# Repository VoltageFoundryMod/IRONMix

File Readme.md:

# IRONMix Eurorack Module

## Overview

Voltage Foundry Modular _IRONMix_ is a dual-function Eurorack Module in 4HP. It is a line in mixer with 2 stereo inputs and Left/Right modular-level outputs and in it's lower section it is an output module with Left/Right modular-level inputs and a stereo output capable of driving headphones or line-level gear.

## Features and Tips

- Two sections which can be used independently or together: a line in section and an output section.
- Line-in section with two stereo inputs, level controls, up to 40dB of gain, and 1MΩ input impedance and left/right modular-level outputs.
- Output section with two modular-level inputs for Left and Right channels, and a stereo output with volume control.
- Line level input is normalized to the output section, allowing the module to be used as a 2 stereo ins to stereo out mixer.
- Input section can be configured to accept line level or modular level signals, allowing the module to be used as a 2x left + 2x right mixer with modular level signals on the inputs and headphone/line level signals on the output.
- Output section right channel can be configured to be normalized to the left channel, allowing mono signals to be turned into stereo signals or normalized to the input section, allowing the module to be used as a 2 stereo ins to stereo out mixer.
- Stereo jacks on input section can be split with a stereo to 2x mono patch cable, allowing the module to be used as a 2x left + 2x right mixer with modular level signals on the inputs and headphone/line level signals on the output.

Check the module on [ModularGrid](https://modulargrid.net/e/other-unknown-ironmix-by-voltage-foundry-modular).

## Usage

For more details and usage instructions, see [Manual.md](Manual.md).

## Contact

For support and inquiries, please open an issue on the [GitHub repository](https://github.com/VoltageFoundryMod/IRONMix).

## License

This project is licensed under the MIT License. See the `LICENSE` file for more information.

---

Thank you for choosing the IRONMix module. We hope it enhances your musical creativity and performance.

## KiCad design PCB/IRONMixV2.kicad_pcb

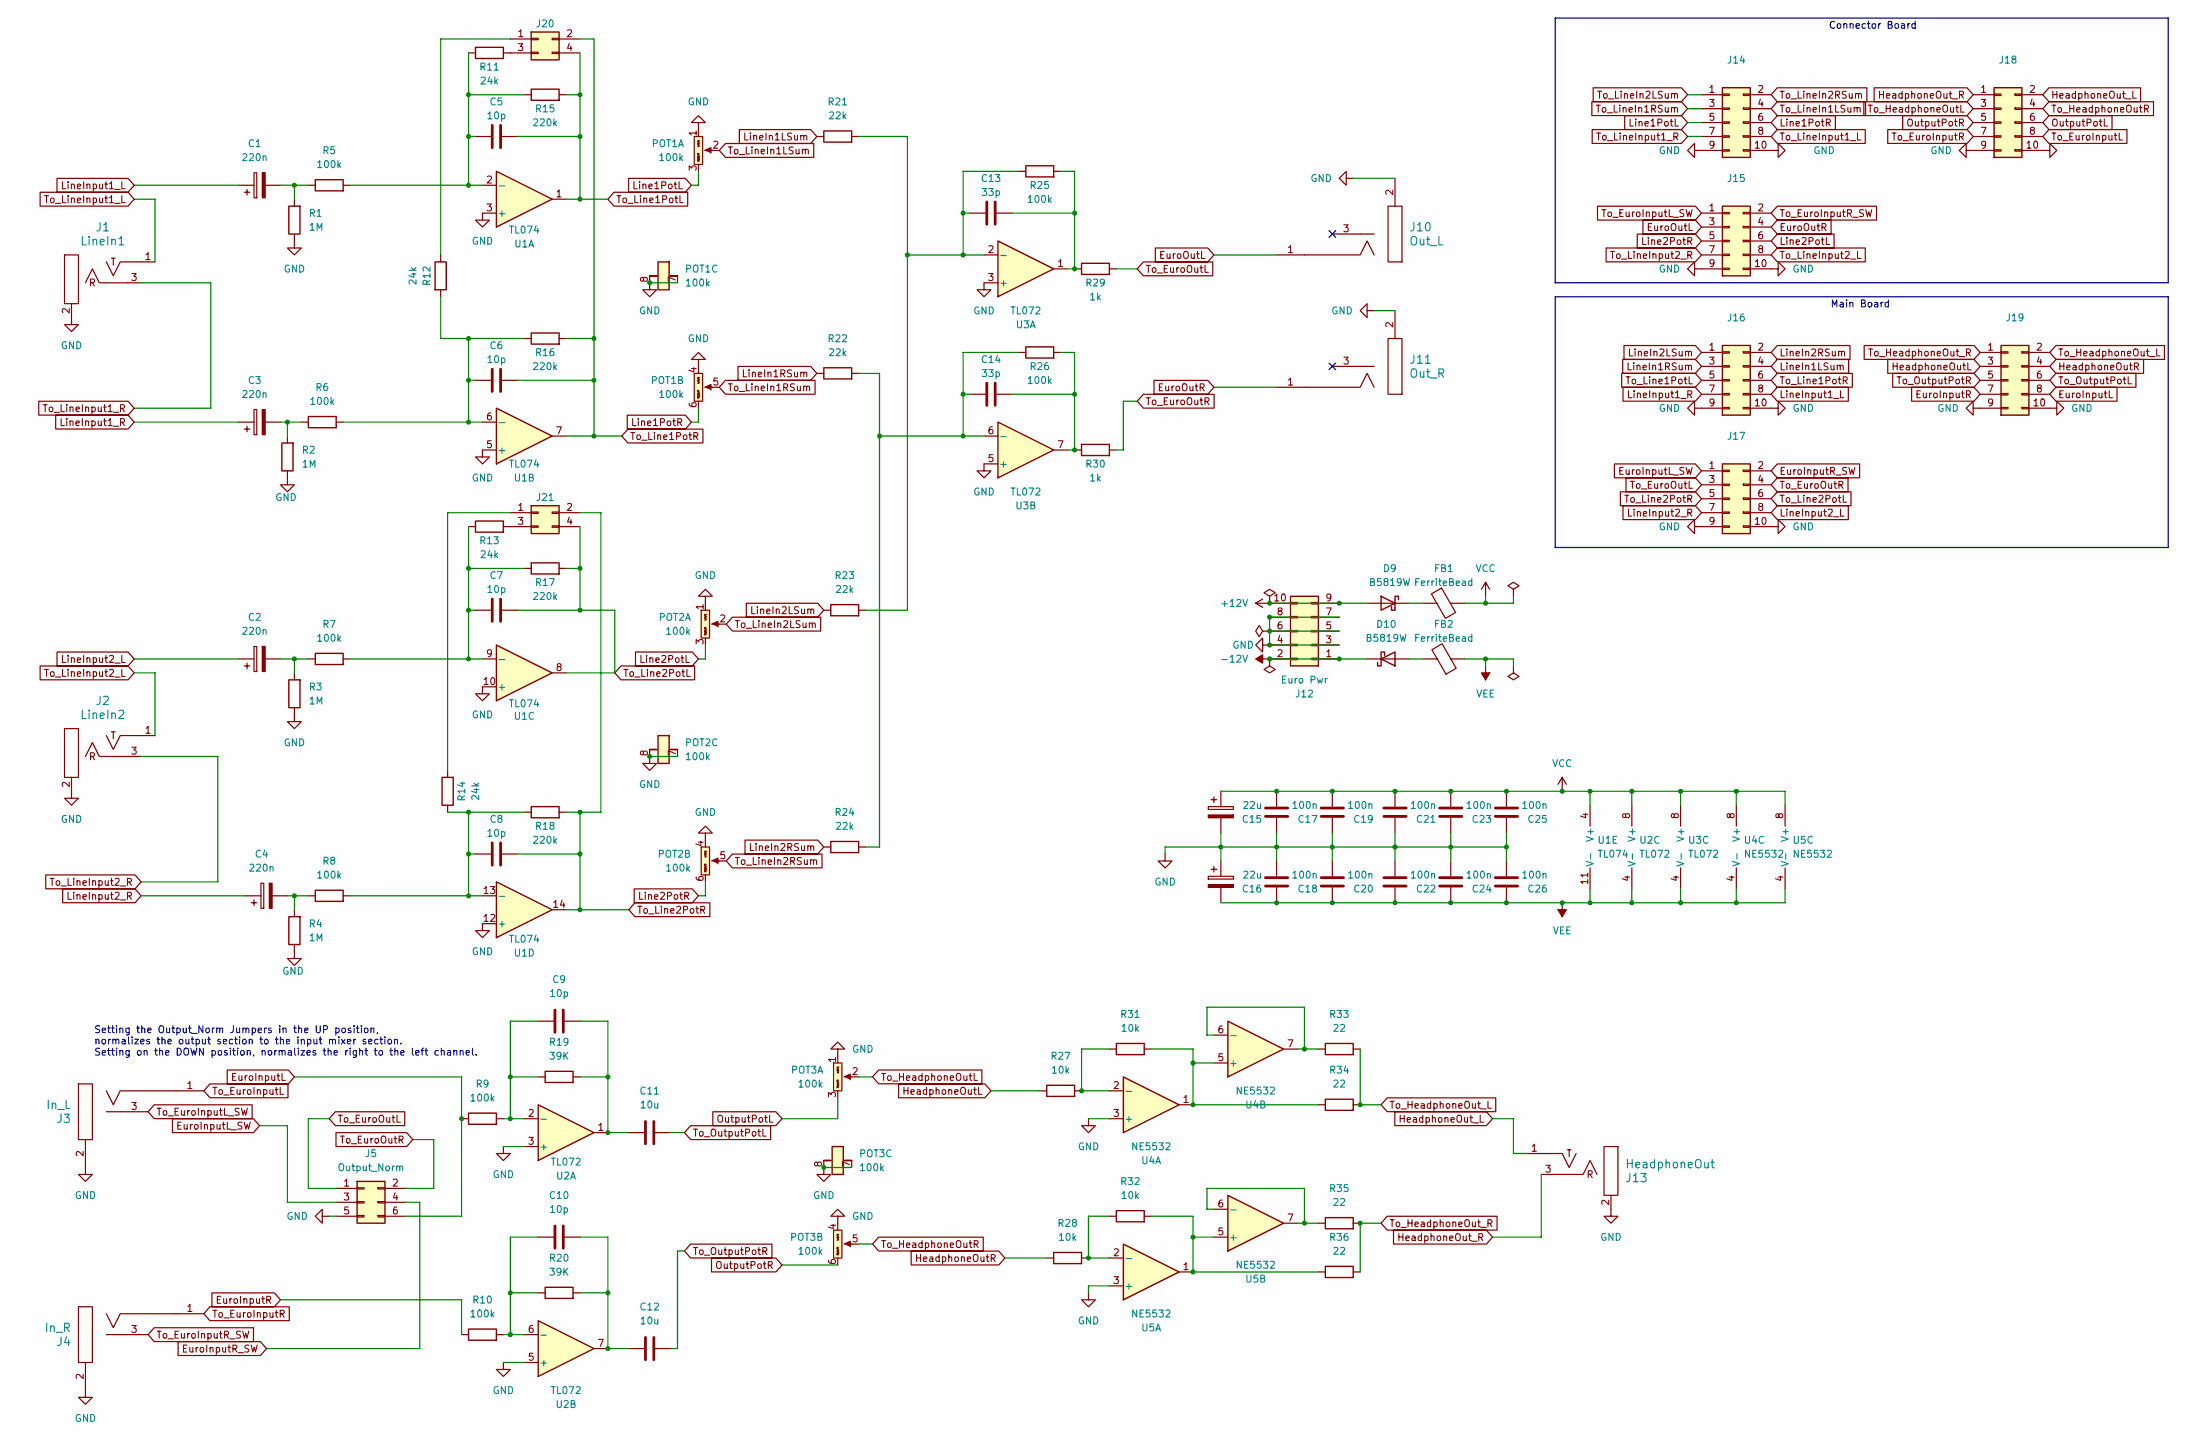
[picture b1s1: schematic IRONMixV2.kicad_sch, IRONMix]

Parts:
C1, C2, C3, C4: 220n; C_0805_2012Metric
C5, C6, C7, C8, C9, C10: 10p; C_0603_1608Metric
C11, C12: 10u; C_0603_1608Metric
C13, C14: 33p; C_0603_1608Metric
C15, C16: 22u; CP_Elec_6.3x4.5
C17, C18, C19, C20, C21, C22, C23, C24, C25, C26: 100n; C_0603_1608Metric
D9, D10: B5819W; D_SOD-123
FB1, FB2: FerriteBead; L_0805_2012Metric
J1: LineIn1; EighthInch_Stereo_PJ366ST; Part Number WQP-WQP419GR
J2: LineIn2; EighthInch_Stereo_PJ366ST; Part Number WQP-WQP419GR
J3: In_L; EighthInch_PJ398SM; Part Number WQP-WQP518MA
J4: In_R; EighthInch_PJ398SM; Part Number WQP-WQP518MA
J5: Output_Norm; PinHeader_2x03_P2.54mm_Vertical; Part Number LL1009-2A, 2.54MM 2*3PIN HEADER,LENGTH=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
J10: Out_L; EighthInch_PJ398SM; Part Number WQP-WQP518MA
J11: Out_R; EighthInch_PJ398SM; Part Number WQP-WQP518MA
J12: Euro Pwr; Pins_2x05_2.54mm_TH_EurorackPower
J13: HeadphoneOut; EighthInch_Stereo_PJ366ST; Part Number WQP-WQP419GR
J14, J15, J18: Socket_02x05_P2.54mm_H5mm_TH; PinHeader_2x05_P2.54mm_Vertical; Part Number CES-110-01-G-D
J16, J17, J19: Socket_02x05_P2.54mm_H5mm_TH; PinSocket_2x05_P2.54mm_Vertical; Part Number CES-110-01-G-D
J20: Line1_Lvl; PinHeader_2x02_P2.54mm_Vertical
J21: Line2_Lvl; PinHeader_2x02_P2.54mm_Vertical
POT1, POT2, POT3: 9mm_Dual_50k_DShaft_DualRow; Potentiometer_Alps_RK09L_Double_Vertical; Part Number 9M2V5BNB-D-15F-B50K-19WE
R1, R2, R3, R4: 1M; R_0603_1608Metric
R5, R6, R7, R8, R9, R10, R25, R26: 100k; R_0603_1608Metric
R11, R12, R13, R14: 24k; R_0603_1608Metric
R15, R16, R17, R18: 220k; R_0603_1608Metric
R19, R20: 39K; R_0603_1608Metric
R21, R22, R23, R24: 22k; R_0603_1608Metric
R27, R28, R31, R32: 10k; R_0603_1608Metric
R29, R30: 1k; R_0603_1608Metric
R33, R34, R35, R36: 22; R_0603_1608Metric
U1: TL074; SOIC-14_3.9x8.7mm_P1.27mm
U2, U3: TL072; SOIC-8_3.9x4.9mm_P1.27mm
U4, U5: NE5532; SOIC-8_3.9x4.9mm_P1.27mm

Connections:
+12V: D9.2 (A), J12.9, J12.10
-12V: D10.1 (K), J12.1, J12.2
EuroInputL: J5.6 (GND), J19.8 (GND), R9.1
EuroInputL_SW: J5.3 (GND), J17.1 (+12V)
EuroInputR: J19.7 (GND), R10.1
EuroInputR_SW: J5.4 (GND), J17.2 (+12V)
EuroOutL: J10.1 (SIG), J15.3 (GND)
EuroOutR: J11.1 (SIG), J15.4 (GND)
GND: C15.2, C16.1, C17.2, C18.1, C19.2, C20.1, C21.2, C22.1, C23.2, C24.1, C25.2, C26.1, J1.2 (SHEILD), J2.2 (SHEILD), J3.2 (SHEILD), J4.2 (SHEILD), J5.5 (GND), J10.2 (SHEILD), J11.2 (SHEILD), J12.3, J12.4, J12.5, J12.6, J12.7, J12.8, J13.2 (SHEILD), J14.9 (-12V), J14.10 (-12V), J15.9 (-12V), J15.10 (-12V), J16.9 (-12V), J16.10 (-12V), J17.9 (-12V), J17.10 (-12V), J18.9 (-12V), J18.10 (-12V), J19.9 (-12V), J19.10 (-12V), POT1.1 (Left), POT1.4 (Left), POT1.7 (SHELL-2), POT1.8 (SHELL-1), POT2.1 (Left), POT2.4 (Left), POT2.7 (SHELL-2), POT2.8 (SHELL-1), POT3.1 (Left), POT3.4 (Left), POT3.7 (SHELL-2), POT3.8 (SHELL-1), R1.1, R2.1, R3.1, R4.1, U1.3 (+), U1.5 (+), U1.10 (+), U1.12 (+), U2.3 (+), U2.5 (+), U3.3 (+), U3.5 (+), U4.3 (+), U5.3 (+)
HeadphoneOutL: J19.3 (GND), R27.1
HeadphoneOutR: J19.4 (GND), R28.1
HeadphoneOut_L: J13.1 (SIG), J18.2 (+12V)
HeadphoneOut_R: J13.3 (SW), J18.1 (+12V)
Line1PotL: J14.5 (GND), POT1.3 (Right)
Line1PotR: J14.6 (GND), POT1.6 (Right)
Line2PotL: J15.6 (GND), POT2.3 (Right)
Line2PotR: J15.5 (GND), POT2.6 (Right)
LineIn1LSum: J16.4 (GND), R21.1
LineIn1RSum: J16.3 (GND), R22.1
LineIn2LSum: J16.1 (+12V), R23.1
LineIn2RSum: J16.2 (+12V), R24.1
LineInput1_L: C1.1, J16.8 (GND)
LineInput1_R: C3.1, J16.7 (GND)
LineInput2_L: C2.1, J17.8 (GND)
LineInput2_R: C4.1, J17.7 (GND)
unnamed: C1.2, R1.2, R5.1
unnamed: C2.2, R3.2, R7.1
unnamed: C3.2, R2.2, R6.1
unnamed: C4.2, R4.2, R8.1
unnamed: C10.2, C12.1, R20.2, U2.7
unnamed: C9.2, C11.1, R19.2, U2.1
unnamed: C13.2, R25.2, R29.1, U3.1
unnamed: C14.2, R26.2, R30.1, U3.7
unnamed: D9.1 (K), FB1.1
unnamed: D10.2 (A), FB2.2
unnamed: J20.1, R12.1
unnamed: J20.3, R11.2
unnamed: J21.1, R14.2
unnamed: J21.3, R13.2
unnamed: C5.1, R5.2, R11.1, R15.1, U1.2 (-)
unnamed: C6.1, R6.2, R12.2, R16.1, U1.6 (-)
unnamed: C7.1, R7.2, R13.1, R17.1, U1.9 (-)
unnamed: C8.1, R8.2, R14.1, R18.1, U1.13 (-)
unnamed: C9.1, R9.2, R19.1, U2.2 (-)
unnamed: C10.1, R10.2, R20.1, U2.6 (-)
unnamed: C13.1, R21.2, R23.2, R25.1, U3.2 (-)
unnamed: C14.1, R22.2, R24.2, R26.1, U3.6 (-)
unnamed: R27.2, R31.1, U4.2 (-)
unnamed: R31.2, R34.1, U4.1, U4.5 (+)
unnamed: R33.1, U4.6 (-), U4.7
unnamed: R28.2, R32.1, U5.2 (-)
unnamed: R32.2, R36.1, U5.1, U5.5 (+)
unnamed: R35.1, U5.6 (-), U5.7
OutputPotL: J18.6 (GND), POT3.3 (Right)
OutputPotR: J18.5 (GND), POT3.6 (Right)
To_EuroInputL: J3.1 (SIG), J18.8 (GND)
To_EuroInputL_SW: J3.3 (SW), J15.1 (+12V)
To_EuroInputR: J4.1 (SIG), J18.7 (GND)
To_EuroInputR_SW: J4.3 (SW), J15.2 (+12V)
To_EuroOutL: J5.1 (+12V), J17.3 (GND), R29.2
To_EuroOutR: J5.2 (+12V), J17.4 (GND), R30.2
To_HeadphoneOutL: J18.3 (GND), POT3.2 (Center)
To_HeadphoneOutR: J18.4 (GND), POT3.5 (Center)
To_HeadphoneOut_L: J19.2 (+12V), R33.2, R34.2
To_HeadphoneOut_R: J19.1 (+12V), R35.2, R36.2
To_Line1PotL: C5.2, J16.5 (GND), J20.4, R15.2, U1.1
To_Line1PotR: C6.2, J16.6 (GND), J20.2, R16.2, U1.7
To_Line2PotL: C7.2, J17.6 (GND), J21.4, R17.2, U1.8
To_Line2PotR: C8.2, J17.5 (GND), J21.2, R18.2, U1.14
To_LineIn1LSum: J14.4 (GND), POT1.2 (Center)
To_LineIn1RSum: J14.3 (GND), POT1.5 (Center)
To_LineIn2LSum: J14.1 (+12V), POT2.2 (Center)
To_LineIn2RSum: J14.2 (+12V), POT2.5 (Center)
To_LineInput1_L: J1.1 (SIG), J14.8 (GND)
To_LineInput1_R: J1.3 (SW), J14.7 (GND)
To_LineInput2_L: J2.1 (SIG), J15.8 (GND)
To_LineInput2_R: J2.3 (SW), J15.7 (GND)
To_OutputPotL: C11.2, J19.6 (GND)
To_OutputPotR: C12.2, J19.5 (GND)
VCC: C15.1, C17.1, C19.1, C21.1, C23.1, C25.1, FB1.2, U1.4 (V+), U2.8 (V+), U3.8 (V+), U4.8 (V+), U5.8 (V+)
VEE: C16.2, C18.2, C20.2, C22.2, C24.2, C26.2, FB2.1, U1.11 (V-), U2.4 (V-), U3.4 (V-), U4.4 (V-), U5.4 (V-)

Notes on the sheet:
Connector Board
Setting the Output_Norm Jumpers in the UP position, normalizes the output section to the input mixer section. Setting on the DOWN position, normalizes the right to the left channel.
Main Board

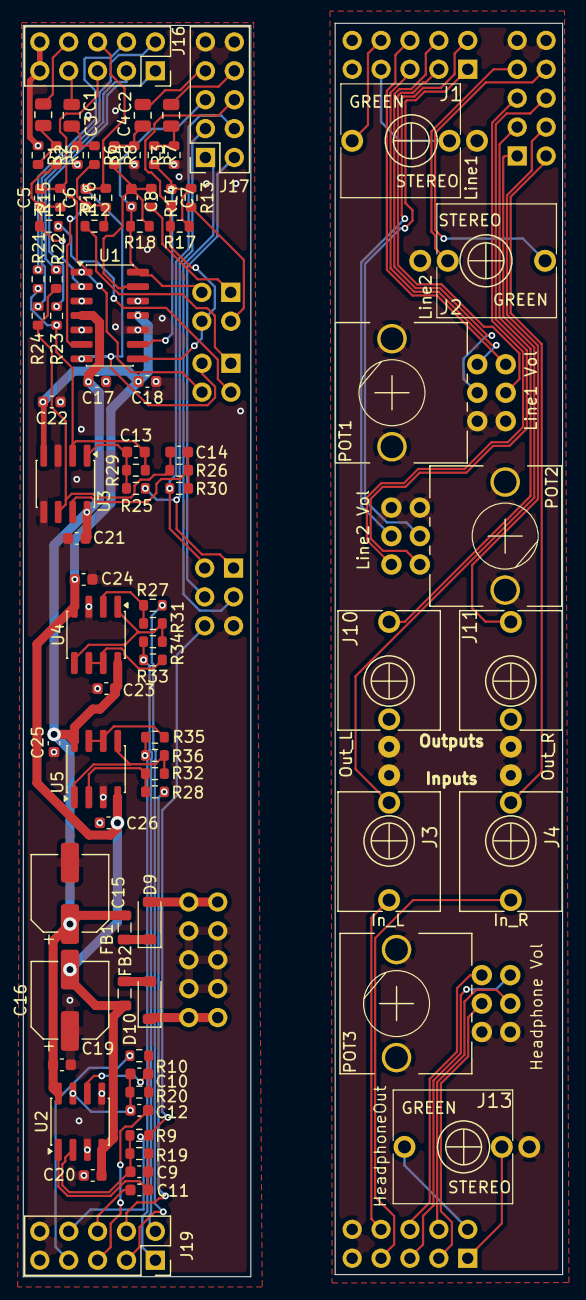
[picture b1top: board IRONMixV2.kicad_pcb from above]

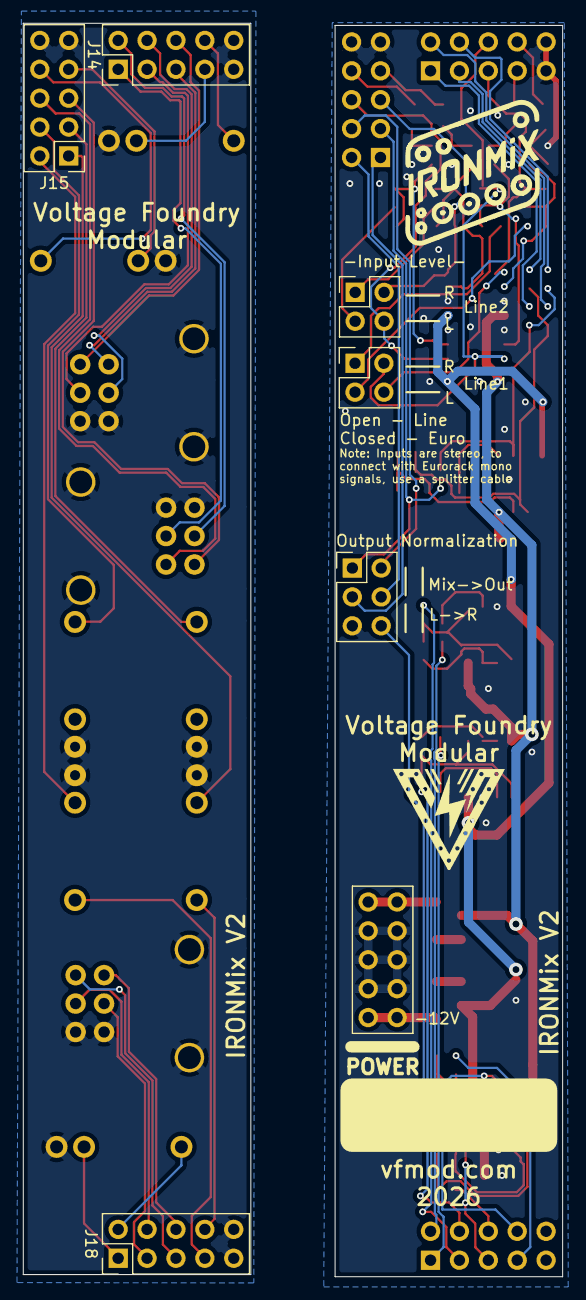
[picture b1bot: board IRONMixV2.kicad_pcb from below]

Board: 2 copper layers, 20.0 x 110.0 mm, 91 parts (7 on the bottom side), 81 nets.

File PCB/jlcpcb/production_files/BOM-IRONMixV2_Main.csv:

Comment,Designator,Footprint,LCSC,Quantity
100k,"R10,R25,R26,R5,R6,R7,R8,R9",R_0603_1608Metric,C25803,8
100n,"C17,C18,C19,C20,C21,C22,C23,C24,C25,C26",C_0603_1608Metric,C14663,10
10k,"R27,R28,R31,R32",R_0603_1608Metric,C25804,4
10p,"C10,C5,C6,C7,C8,C9",C_0603_1608Metric,C1634,6
10u,"C11,C12",C_0603_1608Metric,C96446,2
1M,"R1,R2,R3,R4",R_0603_1608Metric,C22935,4
1k,"R29,R30",R_0603_1608Metric,C21190,2
22,"R33,R34,R35,R36",R_0603_1608Metric,C23345,4
220k,"R15,R16,R17,R18",R_0603_1608Metric,C22961,4
220n,"C1,C2,C3,C4",C_0805_2012Metric,C5378,4
22k,"R21,R22,R23,R24",R_0603_1608Metric,C31850,4
22u,"C15,C16",CP_Elec_6.3x4.5,C5456759,2
24k,"R11,R12,R13,R14",R_0603_1608Metric,C23352,4
33p,"C13,C14",C_0603_1608Metric,C1663,2
39K,"R19,R20",R_0603_1608Metric,C23153,2
B5819W,"D10,D9",D_SOD-123,C8598,2
FerriteBead,"FB1,FB2",L_0805_2012Metric,C1015,2
NE5532,"U4,U5",SOIC-8_3.9x4.9mm_P1.27mm,C7426,2
TL072,"U2,U3",SOIC-8_3.9x4.9mm_P1.27mm,C6961,2
TL074,U1,SOIC-14_3.9x8.7mm_P1.27mm,C6964,1

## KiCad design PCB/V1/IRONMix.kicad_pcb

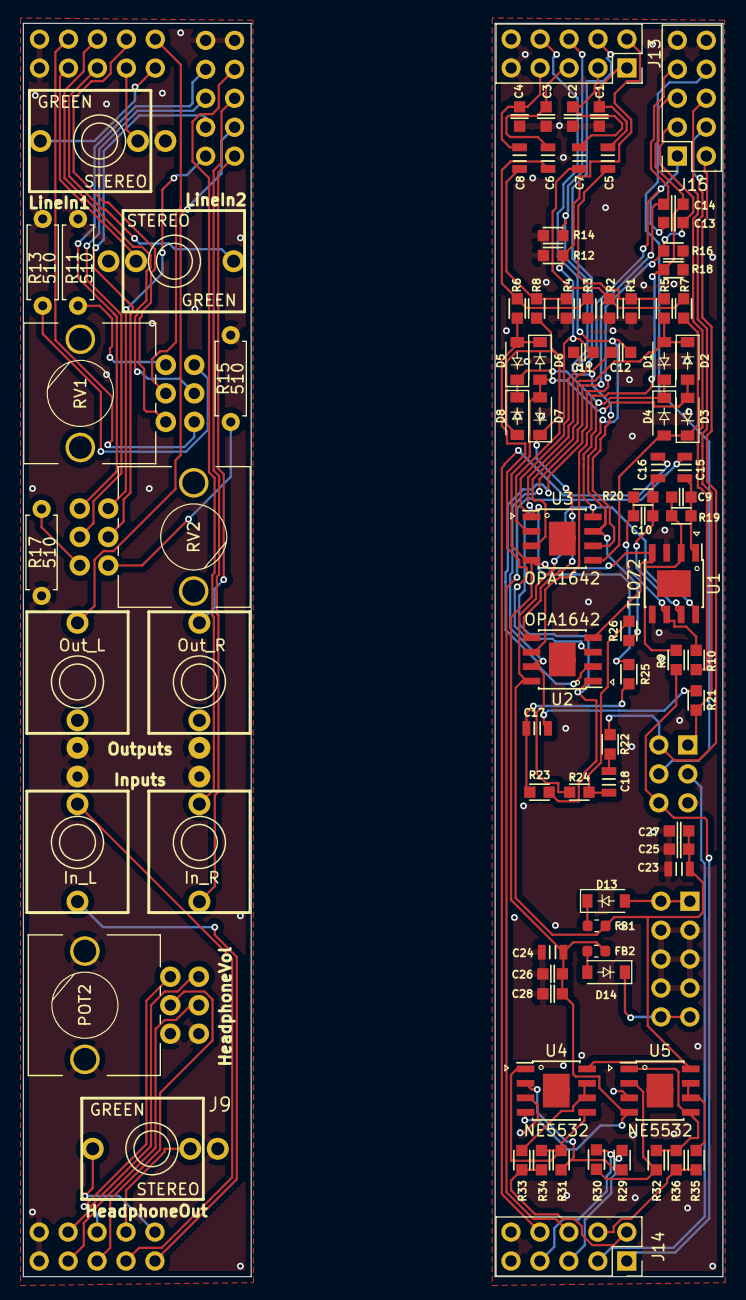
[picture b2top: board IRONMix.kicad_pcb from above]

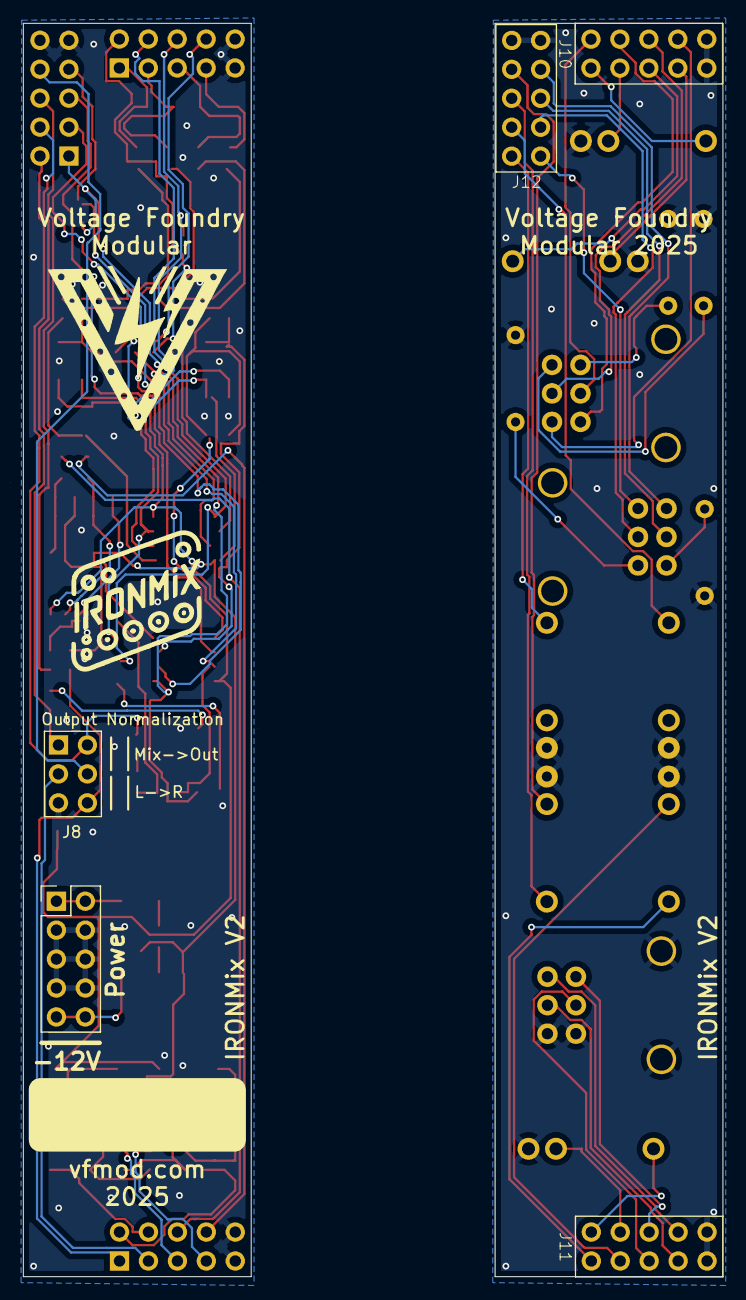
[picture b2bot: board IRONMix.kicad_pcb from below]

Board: 2 copper layers, 20.0 x 110.0 mm, 93 parts (5 on the bottom side), 81 nets.

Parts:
C1, C2, C3, C4: 68p; C_0603
C5, C6, C7, C8, C17, C18: 4.7u; C_0805
C9, C10: 10p; C_0603
C11, C12, C13, C14: 22p; C_0603
C15, C16: 10u; C_0805
C23, C24: 22u; C_0805
C25, C26, C27, C28: 100n; C_0603
D1, D2, D3, D4, D5, D6, D7, D8, D13, D14: B5819W; D_SOD-123
FB1, FB2: FerriteBead; L_0603_1608Metric
J1: LineIn1; EighthInch_Stereo_PJ366ST
J2: LineIn2; EighthInch_Stereo_PJ366ST
J3: In_L; EighthInch_PJ398SM
J4: In_R; EighthInch_PJ398SM
J5: Out_L; EighthInch_PJ398SM
J6: Out_R; EighthInch_PJ398SM
J7: Conn_02x05_Odd_Even; PinHeader_2x05_P2.54mm_Vertical
J8: Output_Norm; Pins_2x03_2.54mm_TH
J9: HeadphoneOut; EighthInch_Stereo_PJ366ST
J10, J11, J12: Socket_02x05_P2.54mm_H5mm_TH; Pins_2x05_2.54mm_TH
J13, J14, J15: Socket_02x05_P2.54mm_H5mm_TH; PinSocket_2x05_P2.54mm_Vertical
POT2: 9mm_Dual_50k_DShaft_DualRow; Potentiometer_Alps_RK09L_Double_Vertical
R1, R2, R3, R4: 1M; R_0603
R5, R6, R7, R8, R12, R14, R16, R18, R23, R24, R25, R26: 10k; R_0603
R9, R10: 100K; R_0603
R11, R13, R15, R17: 510; R_Axial_DIN0207_L6.3mm_D2.5mm_P7.62mm_Horizontal
R19, R20: 39K; R_0603
R21, R22: 510; R_0603
R29, R30, R31, R32: 10K; R_0603
R33, R34, R35, R36: 75; R_0603
RV1, RV2: 50kB; Potentiometer_Alps_RK09L_Double_Vertical
U1: TL072; SOIC-8-1EP_3.9x4.9mm_Pitch1.27mm
U2, U3: OPA1642; SOIC-8-1EP_3.9x4.9mm_Pitch1.27mm
U4, U5: NE5532; SOIC-8-1EP_3.9x4.9mm_Pitch1.27mm

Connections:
+12V: D13.2 (A), J7.1, J7.2
-12V: D14.1 (K), J7.9, J7.10
GND: C1.1, C2.1, C3.1, C4.1, C23.2, C24.1, C25.2, C26.1, C27.2, C28.1, J1.2 (SHEILD), J2.2 (SHEILD), J3.2 (SHEILD), J4.2 (SHEILD), J5.2 (SHEILD), J6.2 (SHEILD), J7.3, J7.4, J7.5, J7.6, J7.7, J7.8, J8.5 (GND), J9.2 (SHEILD), J10.9 (-12V), J10.10 (-12V), J11.9 (-12V), J11.10 (-12V), J12.9 (-12V), J12.10 (-12V), J13.9 (-12V), J13.10 (-12V), J14.9 (-12V), J14.10 (-12V), J15.9 (-12V), J15.10 (-12V), POT2.1 (Left), POT2.4 (Left), POT2.7 (SHELL-2), POT2.8 (SHELL-1), R1.1, R2.1, R3.1, R4.1, R11.1, R12.1, R13.1, R14.1, R15.1, R16.1, R17.1, R18.1, U1.3 (+), U1.5 (+), U4.3 (+), U5.3 (+)
HeadphoneOut_L: J9.1 (SIG), J11.2 (+12V)
HeadphoneOut_L_B: J14.2 (+12V), R33.2, R34.2
HeadphoneOut_PotL_W: J11.5 (GND), POT2.2 (Center)
HeadphoneOut_PotL_W_B: J14.5 (GND), R29.1
HeadphoneOut_PotR_W: J11.7 (GND), POT2.5 (Center)
HeadphoneOut_PotR_W_B: J14.7 (GND), R30.1
HeadphoneOut_R: J9.3 (SW), J11.4 (GND)
HeadphoneOut_R_B: J14.4 (GND), R35.2, R36.2
LineIn1PotL_S: J10.4 (GND), RV1.1
LineIn1PotL_S_B: C11.2, J13.4 (GND), R25.1, U3.1
LineIn1PotL_W: J10.2 (+12V), RV1.2
LineIn1PotL_W_B: C11.1, J13.2 (+12V), R12.2, U3.2 (-)
LineIn1PotR_S: J10.8 (GND), RV1.4
LineIn1PotR_S_B: C12.2, J13.8 (GND), R26.1, U3.7
LineIn1PotR_W: J10.6 (GND), RV1.5
LineIn1PotR_W_B: C12.1, J13.6 (GND), R14.2, U3.6 (-)
LineIn2PotL_S: J12.1 (+12V), RV2.1
LineIn2PotL_S_B: C13.2, J15.1 (+12V), R23.1, U2.1
LineIn2PotL_W: J12.3 (GND), RV2.2
LineIn2PotL_W_B: C13.1, J15.3 (GND), R16.2, U2.2 (-)
LineIn2PotR_S: J12.7 (GND), RV2.4
LineIn2PotR_S_B: C14.2, J15.7 (GND), R24.1, U2.7
LineIn2PotR_W: J12.5 (GND), RV2.5
LineIn2PotR_W_B: C14.1, J15.5 (GND), R18.2, U2.6 (-)
LineInput1_L: J1.1 (SIG), J10.1 (+12V)
LineInput1_L_B: C1.2, C5.1, J13.1 (+12V)
LineInput1_R: J1.3 (SW), J10.3 (GND)
LineInput1_R_B: C2.2, C7.1, J13.3 (GND)
LineInput2_L: J2.1 (SIG), J10.5 (GND)
LineInput2_L_B: C3.2, C6.1, J13.5 (GND)
LineInput2_R: J2.3 (SW), J10.7 (GND)
LineInput2_R_B: C4.2, C8.1, J13.7 (GND)
LineOut_L: J5.1 (SIG), J12.4 (GND)
LineOut_L_B: J8.1 (+12V), J15.4 (GND), R21.2
LineOut_R: J6.1 (SIG), J12.2 (+12V)
LineOut_R_B: J8.2 (+12V), J15.2 (+12V), R22.2
ModInput_L: J3.1 (SIG), J11.1 (+12V)
ModInput_L_B: J8.6 (GND), J14.1 (+12V), R9.1
ModInput_L_SW: J3.3 (SW), J11.3 (GND)
ModInput_L_SW_B: J8.3 (GND), J14.3 (GND)
ModInput_R: J4.1 (SIG), J12.6 (GND)
ModInput_R_B: J15.6 (GND), R10.1
ModInput_R_SW: J4.3 (SW), J12.8 (GND)
ModInput_R_SW_B: J8.4 (GND), J15.8 (GND)
ModPotL_S: J11.6 (GND), POT2.3 (Right)
ModPotL_S_B: C15.2, J14.6 (GND)
ModPotR_S: J11.8 (GND), POT2.6 (Right)
ModPotR_S_B: C16.2, J14.8 (GND)
unnamed: C5.2, R1.2, R5.1
unnamed: C6.2, R3.2, R6.1
unnamed: C7.2, R2.2, R7.1
unnamed: C8.2, R4.2, R8.1
unnamed: C10.2, C16.1, R20.2, U1.7
unnamed: C9.2, C15.1, R19.2, U1.1
unnamed: C17.1, R23.2, R25.2
unnamed: C17.2, R21.1
unnamed: C18.1, R24.2, R26.2
unnamed: C18.2, R22.1
unnamed: D1.2 (A), D2.1 (K), R5.2, U3.3 (+)
unnamed: D3.2 (A), D4.1 (K), R7.2, U3.5 (+)
unnamed: D5.2 (A), D6.1 (K), R6.2, U2.3 (+)
unnamed: D7.2 (A), D8.1 (K), R8.2, U2.5 (+)
unnamed: D13.1 (K), FB1.1
unnamed: D14.2 (A), FB2.2
unnamed: R11.2, RV1.3
unnamed: R13.2, RV1.6
unnamed: R15.2, RV2.3
unnamed: R17.2, RV2.6
unnamed: C9.1, R9.2, R19.1, U1.2 (-)
unnamed: C10.1, R10.2, R20.1, U1.6 (-)
unnamed: R29.2, R31.1, U4.2 (-)
unnamed: R31.2, R34.1, U4.1, U4.5 (+)
unnamed: R33.1, U4.6 (-), U4.7
unnamed: R30.2, R32.1, U5.2 (-)
unnamed: R32.2, R36.1, U5.1, U5.5 (+)
unnamed: R35.1, U5.6 (-), U5.7
VCC: C23.1, C25.1, C27.1, D1.1 (K), D3.1 (K), D5.1 (K), D7.1 (K), FB1.2, U1.8 (V+), U2.8 (V+), U3.8 (V+), U4.8 (V+), U5.8 (V+)
VEE: C24.2, C26.2, C28.2, D2.2 (A), D4.2 (A), D6.2 (A), D8.2 (A), FB2.1, U1.4 (V-), U2.4 (V-), U3.4 (V-), U4.4 (V-), U5.4 (V-)

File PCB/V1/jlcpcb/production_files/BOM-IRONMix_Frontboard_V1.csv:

Comment,Designator,Footprint,LCSC
LineIn2,J2,EighthInch_Stereo_PJ366ST,
LineIn1,J1,EighthInch_Stereo_PJ366ST,
510,R17,R_Axial_DIN0207_L6.3mm_D2.5mm_P7.62mm_Horizontal,
510,R13,R_Axial_DIN0207_L6.3mm_D2.5mm_P7.62mm_Horizontal,
510,R15,R_Axial_DIN0207_L6.3mm_D2.5mm_P7.62mm_Horizontal,
In_L,J3,EighthInch_PJ398SM,
HeadphoneOut,J9,EighthInch_Stereo_PJ366ST,
510,R11,R_Axial_DIN0207_L6.3mm_D2.5mm_P7.62mm_Horizontal,
In_R,J4,EighthInch_PJ398SM,
50kB,RV1,Potentiometer_Alps_RK09L_Double_Vertical,
9mm_Dual_50k_DShaft_DualRow,POT2,Potentiometer_Alps_RK09L_Double_Vertical,
50kB,RV2,Potentiometer_Alps_RK09L_Double_Vertical,
Out_L,J5,EighthInch_PJ398SM,
Out_R,J6,EighthInch_PJ398SM,
Socket_02x05_P2.54mm_H5mm_TH,J12,Socket_2x05_2.54mm_TH,
Socket_02x05_P2.54mm_H5mm_TH,J10,Socket_2x05_2.54mm_TH,
Socket_02x05_P2.54mm_H5mm_TH,J11,Socket_2x05_2.54mm_TH,

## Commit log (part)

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2025-01-29 Initial version with produced V1
2025-01-29 Add LICENSE
2025-01-29 Fix image links
